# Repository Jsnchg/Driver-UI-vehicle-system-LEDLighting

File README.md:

# Driver-UI-vehicle-system-LEDLighting

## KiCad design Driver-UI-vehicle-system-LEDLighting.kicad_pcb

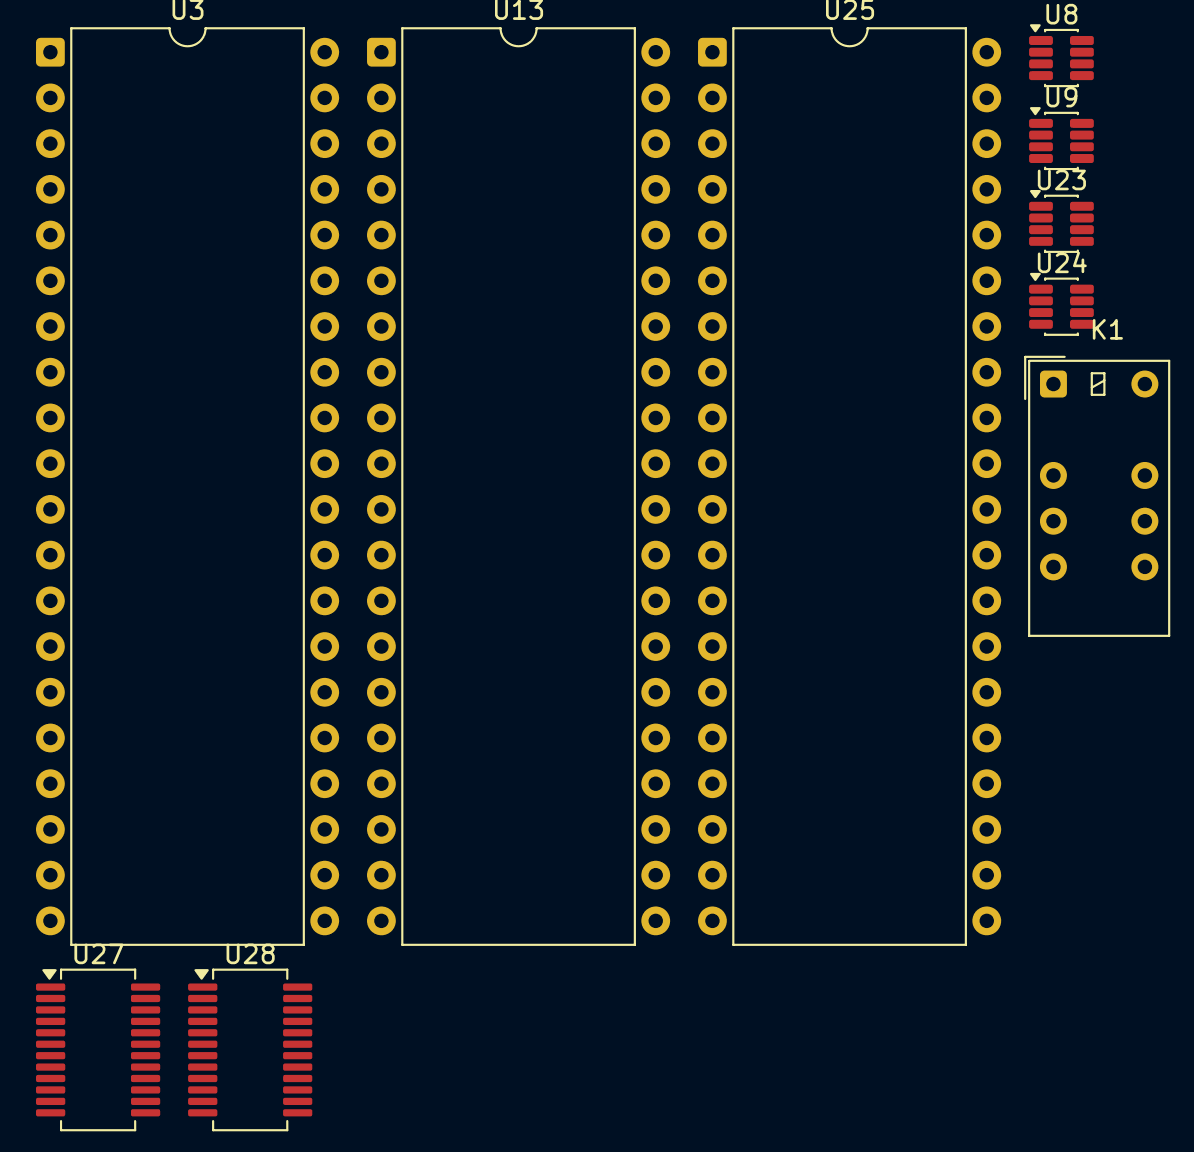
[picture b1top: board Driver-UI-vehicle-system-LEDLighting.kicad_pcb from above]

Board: 2 copper layers, 10 parts (0 on the bottom side), 11 nets, no tracks yet.

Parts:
K1: EC2-3NU; Relay_DPDT_Kemet_EC2_NU
U3, U13, U25: 8080; DIP-40_W15.24mm
U8, U9, U23, U24: MPQ3362GJ-AEC1; TSOT-23-8
U27, U28: LED1642GWPTR; QSOP-24_3.9x8.7mm_P0.635mm

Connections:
unnamed: K1.1, K1.3, K1.5, K1.8, K1.10
unnamed: K1.4, K1.9, K1.12
unnamed: U23.4 (EN), U23.5 (OSC)
unnamed: U23.6 (FB), U23.7 (OVP)
unnamed: U23.8 (GND), U25.11 (-5V)
unnamed: U24.8 (GND), U25.2 (GND)
unnamed: U8.7 (OVP), U27.5 (OUT0)
unnamed: U8.1 (SW), U27.6 (OUT1)
unnamed: U8.6 (FB), U27.24 (VDD)
unnamed: U9.6 (FB), U28.6 (OUT1)
unnamed: U9.7 (OVP), U28.7 (OUT2)

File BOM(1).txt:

Driver-UI-vehicle-system BOM

A. Interior Lighting
1. +12V
2. NCV68261
3. NCV8877
4. NIS6150
5. NSS40201L
6. NCV7685
7. MPQ3362GJ-AEC1 x2
8. LED1642GWPTR x2
9. LED x10
10. 8080
11. NCID9411
12 CAT24C256
13. GND

B. Front LED Lighting
1. +12V
2. NCV68261
3. NCV8877
4. NCV8730
5. NCP3065 x2
6. NCV78247
7. NCV7357
8. EC2-3NU
9. 8080
10. NV25128MUW
11. ESDONCAN1LT
12. GND x2
13. NCV70628
14. NVMFWS004N04XM
15. RotaryEncoder_Switch x1
16. Fan x1


C. Rear LED Lighting
1. +12V x1
2. NCV68261
3. NSS40201L x2
4. NCV7685
5. MPQ3362GJ-AEC1 x2
6. LED x10
7. 8080
8. NCV7351 
9. NV2512BMUW
10 GND x1

Total:
1. +12V x3
2. NCV68261 x3
3. NCV8877 x2
4. NIS6150 x1
5. NSS40201L x3
6. NCV7685 x2
7. MPQ3362GJ-AEC1 x4
8. LED1642GWPTR x2
9. LED x20
10. 8080 x3
11. NCID9411 x1
12. CAT24C256 x1
13. GND x4 x1
14. NCV8730 x1
15. NCP3065 x2
16. NCV78247 x1
17. NCV7357 x1
18. EC2-3NU x1
19. NV25128MUW x2
20. ESDONCAN1LT x1
21. NCV70628 x1
22. NVMFWS004N04XM x1
23. RotaryEncoder_Switch x1
24. Fan x1
25. NCV7351 x1

*Remark: 10 LED's where added in both Interior Lighting and Rear LED Lighting. Fan, RotaryEncoder_Switch, EC2-3NU and 2 LED's were added into Front LED Lighting.
2 MPQ3362GJ-AEC1 and 2 LED1642GWPTR. All these were added to personalize the project (All inspiration credits goes to Onsemi)
